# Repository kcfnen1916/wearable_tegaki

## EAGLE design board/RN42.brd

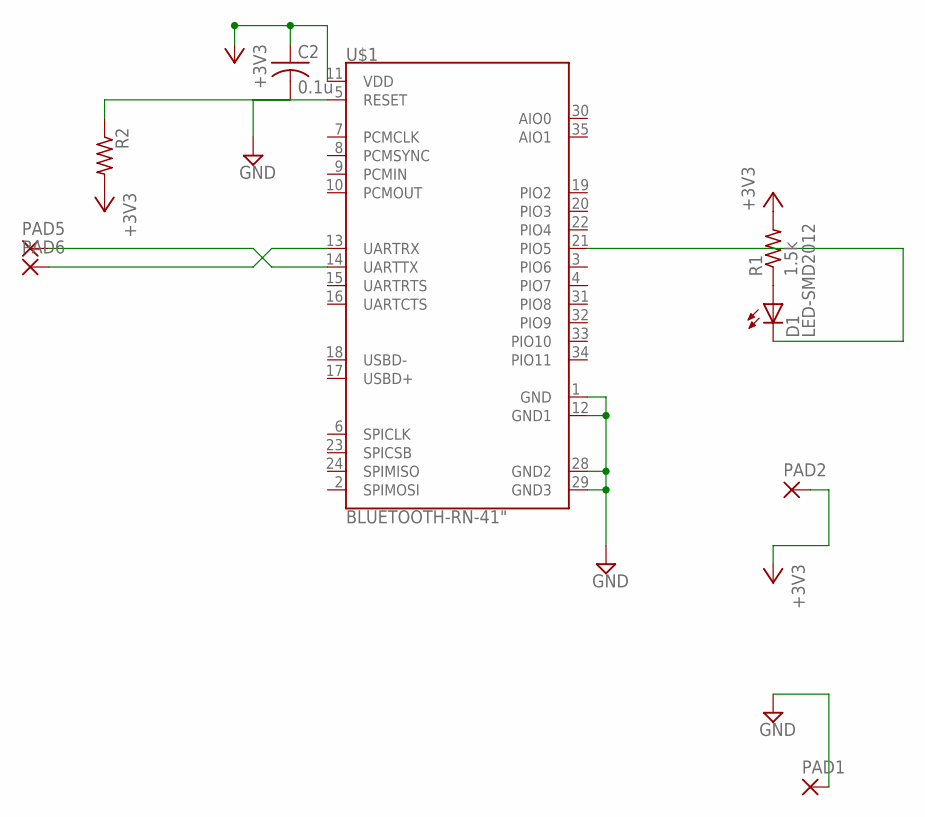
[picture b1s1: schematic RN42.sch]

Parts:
C2: 0.1u; 2012-C
D1: LED-SMD2012; D2012
PAD1, PAD2, PAD5, PAD6: SMD5; SMD2,54-5,08
R1: 1.5k; 2012-R
R2: 10k; 2012-R
U$1: BLUETOOTH-RN-41"; RN41

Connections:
+3V3: C2.1, PAD2.1, R1.2, R2.2, U$1.11 (VDD)
GND: C2.2, PAD1.1, U$1.1 (GND), U$1.12 (GND1), U$1.28 (GND2), U$1.29 (GND3)
unnamed: D1.K, U$1.21 (PIO5)
unnamed: D1.A, R1.1
unnamed: PAD5.1, U$1.14 (UARTTX)
unnamed: R2.1, U$1.5 (RESET)
unnamed: PAD6.1, U$1.13 (UARTRX)

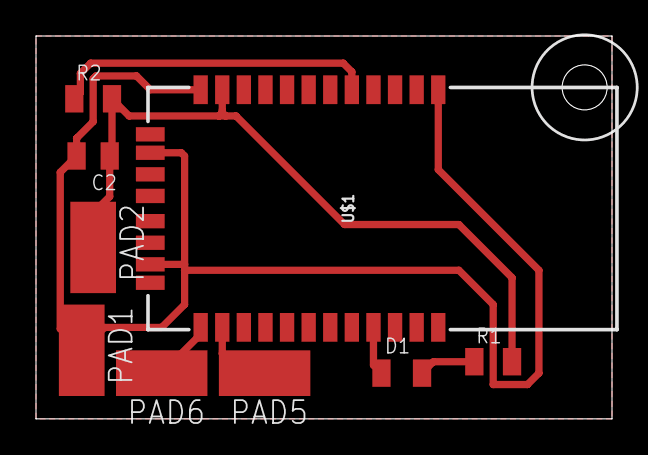
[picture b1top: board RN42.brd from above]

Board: 2 copper layers, 32.0 x 21.3 mm, 10 parts (0 on the bottom side), 7 nets.

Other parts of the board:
U$2: DRIL-2,5

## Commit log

2019-08-06 8/6 Demo時点
2019-08-07 何も変えていません
2019-08-07 add extract_alphabet_data
2019-08-07 いらないファイルを削除
2019-08-08 raspi mpr121 test
2019-08-08 wearable α
2019-08-09 時間のところをデバッグした(入力が早くなった)
2019-08-10 一度うまくいった
2019-08-10 solved
2019-08-10 try python3 nazoru-input -g ./my_data_test/optimized_nazoru.pb
2019-08-10 add requirements.txt
2019-08-11 improved keyboard_recorder.py
2019-08-11 学習データ生成コード
2019-08-12 improved mktraindata.py
2019-08-17 フリック実装
2019-08-17 フリックバグ修正
2019-08-17 デバッグ用に修正
2019-08-18 flickできた
2019-08-18 MPR121で学習できるように変更
2019-08-20 add BlogCode
2019-08-20 modify
2019-08-20 入力ジェスチャー判定を改善
2019-08-20 学習改善
2019-08-20 test
2019-08-20 indent
2019-08-20 change print
2019-08-22 change number
2019-08-26 flichと手書きマージ
2019-08-26 染谷研サンプルでのフリック動作を確認
2019-08-26 comment削除
2019-08-27 esp32ピン変更
2019-08-29 flick interim examination
2019-09-02 bluetooth
2019-09-02 Bluetooth組み込み
2019-09-02 delete実装
2019-09-03 backspace
2019-09-03 socket
2019-09-03 socket2
2019-09-03 socket3
2019-09-03 socket5
2019-09-03 change port number
2019-09-03 change lan
2019-09-03 copy shinoda branch
2019-09-05 encode-decode
2019-09-05 list on main.py
2019-09-10 change close
2019-09-10 aws test
2019-09-10 change nazoru-input
2019-09-10 anzai
2019-09-12 矢印キー実装
2019-09-12 complete
2019-09-13 add requirement
2019-09-13 change gesture
2019-09-15 add while
2019-09-15 コマンドライン引数に対応
2019-09-15 right left fix
2019-09-15 手書き入力でのコマンド送信
2019-09-16 anzaidata
2019-09-16 rm_trainingdata
2019-09-16 大岸：CAD追加
2019-09-16 mkdir
2019-09-17 shinoda_data
2019-09-17 学習のために一旦coreの中のrecorderをコメントアウトしています
2019-09-17 学習した
2019-09-17 add removed
2019-09-17 精度が上がった
2019-09-17 coreを戻した
2019-09-17 flick_ver2.0
2019-09-17 fix_flick_ver2.0
2019-09-24 waittime平均化
2019-09-25 矢印キーのみにした
2019-09-28 学習データ追加9/27
2019-09-28 merged strokes
2019-09-28 多少違うところ押してもいいように修正
2019-09-28 core修正
2019-09-28 new data
2019-09-28 removeし直したデータ
2019-09-28 add model
2019-09-28 add model 4
2019-09-28 rだけのデータ
2019-10-07 offset
2019-10-08 gitignore追加
2019-10-21 c言語移行途中
2019-10-29 コンパイル通った
2019-11-02 昨日の編集
2019-11-02 Bump pillow from 6.1.0 to 6.2.0 in /mozc-nazoru
    Bumps [pillow](https://github.com/python-pillow/Pillow) from 6.1.0 to 6.2.0.
    - [Release notes](https://github.com/python-pillow/Pillow/releases)
    - [Changelog](https://github.com/python-pillow/Pillow/blob/master/CHANGES.rst)
    - [Commits](https://github.com/python-pillow/Pillow/compare/6.1.0...6.2.0)
2019-11-06 学習データ作り
2019-11-06 とりあえず
2019-11-10 for m5stick_test
2019-11-14 libを変更、test用のコードを追加
2019-11-14 バグ修正
2019-11-15 とりあえず完成
2019-11-15 make config_to_c.py
2019-11-15 ルールを追加
2019-11-15 config生成
2019-11-15 ルールベースの手書き
2019-11-15 ルールベース修正
2019-11-15 ルール追加
2019-11-15 mode切替を修正
2019-11-23 配列を作れるようにした
2019-12-03 大文字以外完成
2019-12-04 new_config.cpp
2019-12-04 M5Stick用
2019-12-06 blekeyboard修正
2019-12-06 手書きに対応
2019-12-06 矢印キーのみ
2019-12-06 .clangformat追加
2019-12-07 blekeyboard設定
2019-12-16 コメントアウト削除
2019-12-16 Bump tensorflow from 1.14.0 to 1.15.0 in /mozc-nazoru
    Bumps [tensorflow](https://github.com/tensorflow/tensorflow) from 1.14.0 to 1.15.0.
    - [Release notes](https://github.com/tensorflow/tensorflow/releases)
    - [Changelog](https://github.com/tensorflow/tensorflow/blob/master/RELEASE.md)
    - [Commits](https://github.com/tensorflow/tensorflow/compare/v1.14.0...v1.15.0)
2019-12-24 GUGEN修正
2019-12-24 kとhの識別でっち上げ
2019-12-26 ルールを修正
2019-12-31 levenshtein距離による判定
2019-12-31 テスト用のコードに変えた
2019-12-31 levenshtein距離 修正版
2019-12-31 xbly微修正
2019-12-31 levenshtein距離 修正版 handwritingをaddした
2019-12-31 levenshtein距離 修正版 guardを入れた
2020-01-01 recordまで
2020-01-01 gch削除
2020-01-01 gitignoreにgch追加
2020-01-28 Bump tensorflow from 1.14.0 to 1.15.2 in /mozc-nazoru
    Bumps [tensorflow](https://github.com/tensorflow/tensorflow) from 1.14.0 to 1.15.2.
    - [Release notes](https://github.com/tensorflow/tensorflow/releases)
    - [Changelog](https://github.com/tensorflow/tensorflow/blob/master/RELEASE.md)
    - [Commits](https://github.com/tensorflow/tensorflow/compare/v1.14.0...v1.15.2)
2020-01-31 一番最初の文字に重みを追加 正規化を追加
2020-01-31 さっきまでの変更は一部やめて元に戻した
2020-01-31 よくわからないファイルを消した
2020-02-05 誤動作を解決,重みを5から2に変更
2020-02-09 merge
2020-02-13 deleteやspaceが機能しないバグを修正
2020-02-24 tweet
2020-02-24 tweetを少し改良
2020-02-26 画面に表示させるのと統合
2020-02-26 音出したりできるようにした
2020-02-27 色々変えた
2020-03-01 シリアル通信コードを変更
2020-03-04 有線用完成のつもり
2020-03-04 無線一応完成
2020-03-04 無線できてる 展示会では有線でも無線でもこっちを使えば良い。Bluetoothキーボードとして使いたいときはsanoブランチ
2020-03-16 色々変更
2020-06-29 静電容量センサを認識しないバグを解消
2020-06-29 いらない行を消した
2020-06-29 少し変更
2020-09-26 Bump tensorflow from 1.14.0 to 1.15.4 in /mozc-nazoru
    Bumps [tensorflow](https://github.com/tensorflow/tensorflow) from 1.14.0 to 1.15.4.
    - [Release notes](https://github.com/tensorflow/tensorflow/releases)
    - [Changelog](https://github.com/tensorflow/tensorflow/blob/master/RELEASE.md)
    - [Commits](https://github.com/tensorflow/tensorflow/compare/v1.14.0...v1.15.4)
2021-03-19 Bump pillow from 6.1.0 to 8.1.1 in /mozc-nazoru
    Bumps [pillow](https://github.com/python-pillow/Pillow) from 6.1.0 to 8.1.1.
    - [Release notes](https://github.com/python-pillow/Pillow/releases)
    - [Changelog](https://github.com/python-pillow/Pillow/blob/master/CHANGES.rst)
    - [Commits](https://github.com/python-pillow/Pillow/compare/6.1.0...8.1.1)
2021-03-25 Bump pyyaml from 5.1.2 to 5.4 in /mozc-nazoru
    Bumps [pyyaml](https://github.com/yaml/pyyaml) from 5.1.2 to 5.4.
    - [Release notes](https://github.com/yaml/pyyaml/releases)
    - [Changelog](https://github.com/yaml/pyyaml/blob/master/CHANGES)
    - [Commits](https://github.com/yaml/pyyaml/compare/5.1.2...5.4)
2021-05-21 Bump tensorflow from 1.14.0 to 2.5.0 in /mozc-nazoru
    Bumps [tensorflow](https://github.com/tensorflow/tensorflow) from 1.14.0 to 2.5.0.
    - [Release notes](https://github.com/tensorflow/tensorflow/releases)
    - [Changelog](https://github.com/tensorflow/tensorflow/blob/master/RELEASE.md)
    - [Commits](https://github.com/tensorflow/tensorflow/compare/v1.14.0...v2.5.0)
2021-06-08 Bump pillow from 6.1.0 to 8.2.0 in /mozc-nazoru
    Bumps [pillow](https://github.com/python-pillow/Pillow) from 6.1.0 to 8.2.0.
    - [Release notes](https://github.com/python-pillow/Pillow/releases)
    - [Changelog](https://github.com/python-pillow/Pillow/blob/master/CHANGES.rst)
    - [Commits](https://github.com/python-pillow/Pillow/compare/6.1.0...8.2.0)
    ---
    updated-dependencies:
2021-08-25 Bump tensorflow from 1.14.0 to 2.5.1 in /mozc-nazoru
    Bumps [tensorflow](https://github.com/tensorflow/tensorflow) from 1.14.0 to 2.5.1.
    - [Release notes](https://github.com/tensorflow/tensorflow/releases)
    - [Changelog](https://github.com/tensorflow/tensorflow/blob/master/RELEASE.md)
    - [Commits](https://github.com/tensorflow/tensorflow/compare/v1.14.0...v2.5.1)
    ---
    updated-dependencies:
2021-09-08 Bump pillow from 6.1.0 to 8.3.2 in /mozc-nazoru
    Bumps [pillow](https://github.com/python-pillow/Pillow) from 6.1.0 to 8.3.2.
    - [Release notes](https://github.com/python-pillow/Pillow/releases)
    - [Changelog](https://github.com/python-pillow/Pillow/blob/master/CHANGES.rst)
    - [Commits](https://github.com/python-pillow/Pillow/compare/6.1.0...8.3.2)
    ---
    updated-dependencies:
2022-01-13 Bump pillow from 6.1.0 to 9.0.0 in /mozc-nazoru
    Bumps [pillow](https://github.com/python-pillow/Pillow) from 6.1.0 to 9.0.0.
    - [Release notes](https://github.com/python-pillow/Pillow/releases)
    - [Changelog](https://github.com/python-pillow/Pillow/blob/main/CHANGES.rst)
    - [Commits](https://github.com/python-pillow/Pillow/compare/6.1.0...9.0.0)
    ---
    updated-dependencies:
2022-02-10 Bump tensorflow from 1.14.0 to 2.5.3 in /mozc-nazoru
    Bumps [tensorflow](https://github.com/tensorflow/tensorflow) from 1.14.0 to 2.5.3.
    - [Release notes](https://github.com/tensorflow/tensorflow/releases)
    - [Changelog](https://github.com/tensorflow/tensorflow/blob/master/RELEASE.md)
    - [Commits](https://github.com/tensorflow/tensorflow/compare/v1.14.0...v2.5.3)
    ---
    updated-dependencies:
2022-02-11 Bump protobuf from 3.9.1 to 3.15.0 in /mozc-nazoru
    Bumps [protobuf](https://github.com/protocolbuffers/protobuf) from 3.9.1 to 3.15.0.
    - [Release notes](https://github.com/protocolbuffers/protobuf/releases)
    - [Changelog](https://github.com/protocolbuffers/protobuf/blob/master/generate_changelog.py)
    - [Commits](https://github.com/protocolbuffers/protobuf/compare/v3.9.1...v3.15.0)
    ---
    updated-dependencies:
2022-03-11 Bump pillow from 6.1.0 to 9.0.1 in /mozc-nazoru
    Bumps [pillow](https://github.com/python-pillow/Pillow) from 6.1.0 to 9.0.1.
    - [Release notes](https://github.com/python-pillow/Pillow/releases)
    - [Changelog](https://github.com/python-pillow/Pillow/blob/main/CHANGES.rst)
    - [Commits](https://github.com/python-pillow/Pillow/compare/6.1.0...9.0.1)
    ---
    updated-dependencies:
2022-05-24 Bump tensorflow from 1.14.0 to 2.6.4 in /mozc-nazoru
    Bumps [tensorflow](https://github.com/tensorflow/tensorflow) from 1.14.0 to 2.6.4.
    - [Release notes](https://github.com/tensorflow/tensorflow/releases)
    - [Changelog](https://github.com/tensorflow/tensorflow/blob/master/RELEASE.md)
    - [Commits](https://github.com/tensorflow/tensorflow/compare/v1.14.0...v2.6.4)
    ---
    updated-dependencies:
2022-05-26 Bump tensorflow from 1.14.0 to 2.7.2 in /mozc-nazoru
    Bumps [tensorflow](https://github.com/tensorflow/tensorflow) from 1.14.0 to 2.7.2.
    - [Release notes](https://github.com/tensorflow/tensorflow/releases)
    - [Changelog](https://github.com/tensorflow/tensorflow/blob/master/RELEASE.md)
    - [Commits](https://github.com/tensorflow/tensorflow/compare/v1.14.0...v2.7.2)
    ---
    updated-dependencies:
2022-06-21 Bump numpy from 1.17.0 to 1.22.0 in /mozc-nazoru
    Bumps [numpy](https://github.com/numpy/numpy) from 1.17.0 to 1.22.0.
    - [Release notes](https://github.com/numpy/numpy/releases)
    - [Changelog](https://github.com/numpy/numpy/blob/main/doc/HOWTO_RELEASE.rst)
    - [Commits](https://github.com/numpy/numpy/compare/v1.17.0...v1.22.0)
    ---
    updated-dependencies:
2022-09-23 Bump protobuf from 3.9.1 to 3.18.3 in /mozc-nazoru
    Bumps [protobuf](https://github.com/protocolbuffers/protobuf) from 3.9.1 to 3.18.3.
    - [Release notes](https://github.com/protocolbuffers/protobuf/releases)
    - [Changelog](https://github.com/protocolbuffers/protobuf/blob/main/generate_changelog.py)
    - [Commits](https://github.com/protocolbuffers/protobuf/compare/v3.9.1...v3.18.3)
    ---
    updated-dependencies:
2022-11-21 Bump tensorflow from 1.14.0 to 2.9.3 in /mozc-nazoru
    Bumps [tensorflow](https://github.com/tensorflow/tensorflow) from 1.14.0 to 2.9.3.
    - [Release notes](https://github.com/tensorflow/tensorflow/releases)
    - [Changelog](https://github.com/tensorflow/tensorflow/blob/master/RELEASE.md)
    - [Commits](https://github.com/tensorflow/tensorflow/compare/v1.14.0...v2.9.3)
    ---
    updated-dependencies:
2022-11-22 Bump pillow from 6.1.0 to 9.3.0 in /mozc-nazoru
    Bumps [pillow](https://github.com/python-pillow/Pillow) from 6.1.0 to 9.3.0.
    - [Release notes](https://github.com/python-pillow/Pillow/releases)
    - [Changelog](https://github.com/python-pillow/Pillow/blob/main/CHANGES.rst)
    - [Commits](https://github.com/python-pillow/Pillow/compare/6.1.0...9.3.0)
    ---
    updated-dependencies:

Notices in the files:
parts and their libraries:
SparkFun-RF: Licensing: Creative Commons ShareAlike 4.0 International - https://creativecommons.org/licenses/by-sa/4.0
